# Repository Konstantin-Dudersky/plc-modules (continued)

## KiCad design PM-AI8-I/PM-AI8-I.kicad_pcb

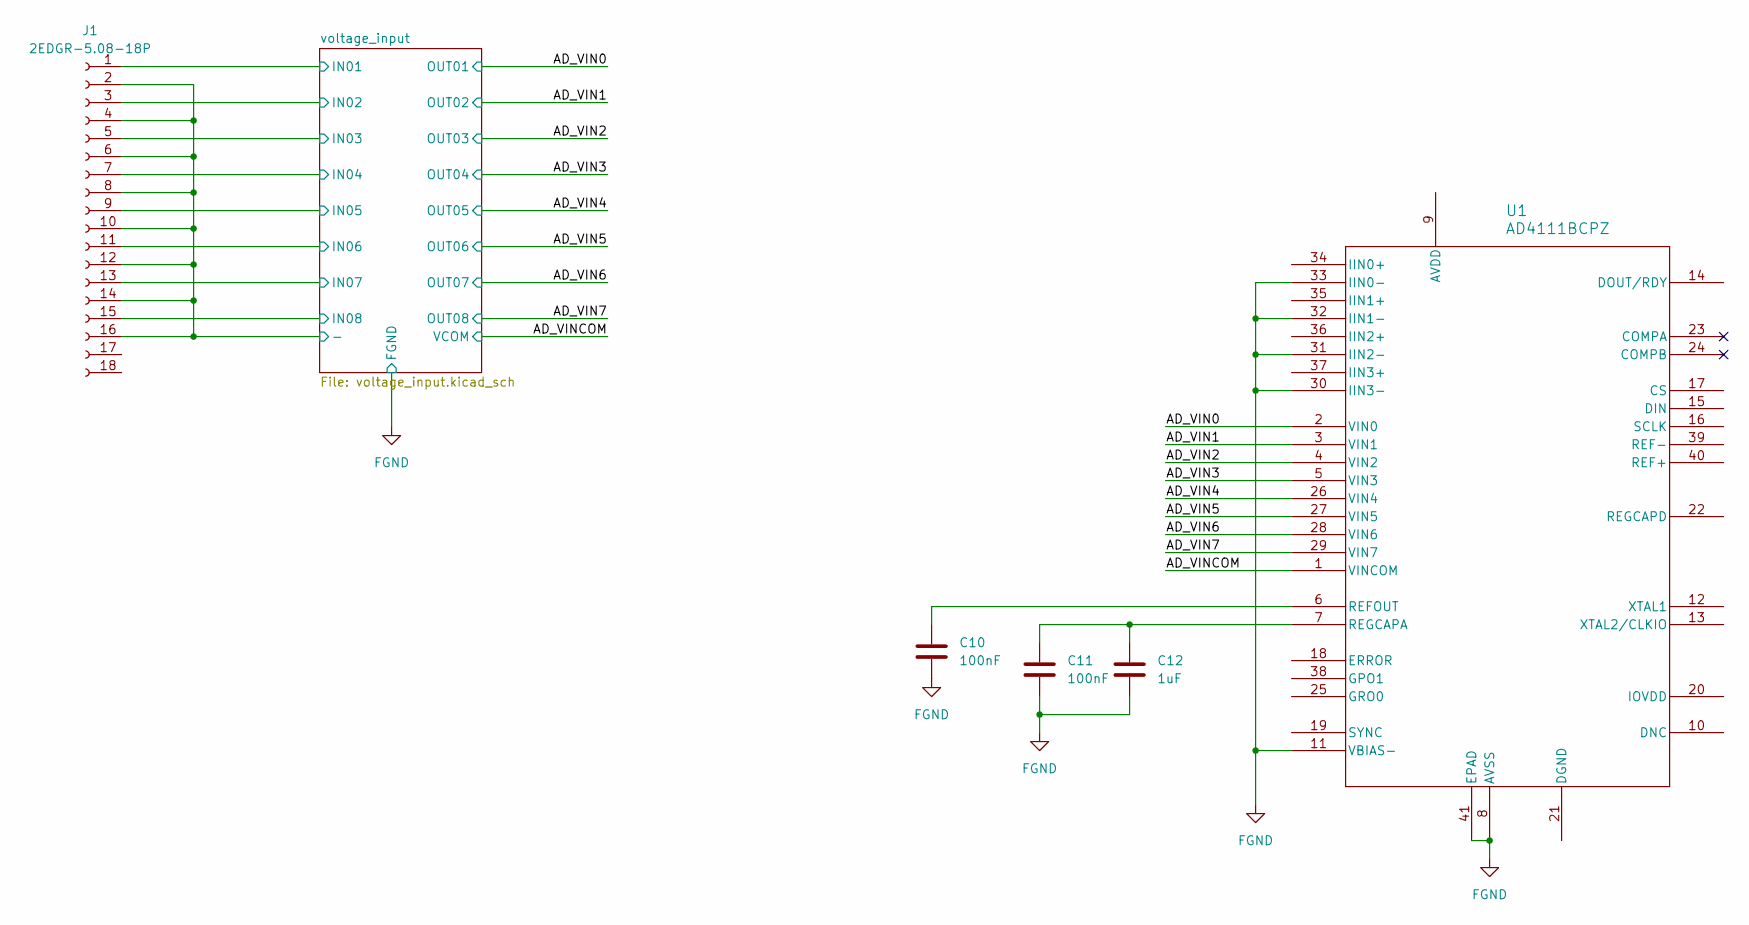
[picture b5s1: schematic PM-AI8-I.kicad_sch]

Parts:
C10, C11: 100nF; C_1206_3216Metric_Pad1.33x1.80mm_HandSolder; part_ipn C_100nF_50V_1206
C12: 1uF; C_1206_3216Metric_Pad1.33x1.80mm_HandSolder; part_ipn C_1uF_50V_1206
J1: 2EDGR-5.08-18P; Degson_2EDGR-5.08-18P; part_ipn 2EDGR-5.08-18P
U1: AD4111BCPZ; AD4111BCPZ_ADI; part_ipn AD4111BCPZ

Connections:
/AD_VIN0: U1.2 (VIN0); also elsewhere on the board
/AD_VIN1: U1.3 (VIN1); also elsewhere on the board
/AD_VIN2: U1.4 (VIN2); also elsewhere on the board
/AD_VIN3: U1.5 (VIN3); also elsewhere on the board
/AD_VIN4: U1.26 (VIN4); also elsewhere on the board
/AD_VIN5: U1.27 (VIN5); also elsewhere on the board
/AD_VIN6: U1.28 (VIN6); also elsewhere on the board
/AD_VIN7: U1.29 (VIN7); also elsewhere on the board
/AD_VINCOM: U1.1 (VINCOM); also elsewhere on the board
/voltage_input/IN01: J1.1; also elsewhere on the board
/voltage_input/IN02: J1.3; also elsewhere on the board
/voltage_input/IN03: J1.5; also elsewhere on the board
/voltage_input/IN04: J1.7; also elsewhere on the board
/voltage_input/IN05: J1.9; also elsewhere on the board
/voltage_input/IN06: J1.11; also elsewhere on the board
/voltage_input/IN07: J1.13; also elsewhere on the board
/voltage_input/IN08: J1.15; also elsewhere on the board
FGND: C10.2, C11.2, C12.2, J1.2, J1.4, J1.6, J1.8, J1.10, J1.12, J1.14, J1.16, U1.8 (AVSS), U1.11 (VBIAS-), U1.30 (IIN3-), U1.31 (IIN2-), U1.32 (IIN1-), U1.33 (IIN0-), U1.41 (EPAD); also elsewhere on the board
unnamed: C10.1, U1.6 (REFOUT)
unnamed: C11.1, C12.1, U1.7 (REGCAPA)

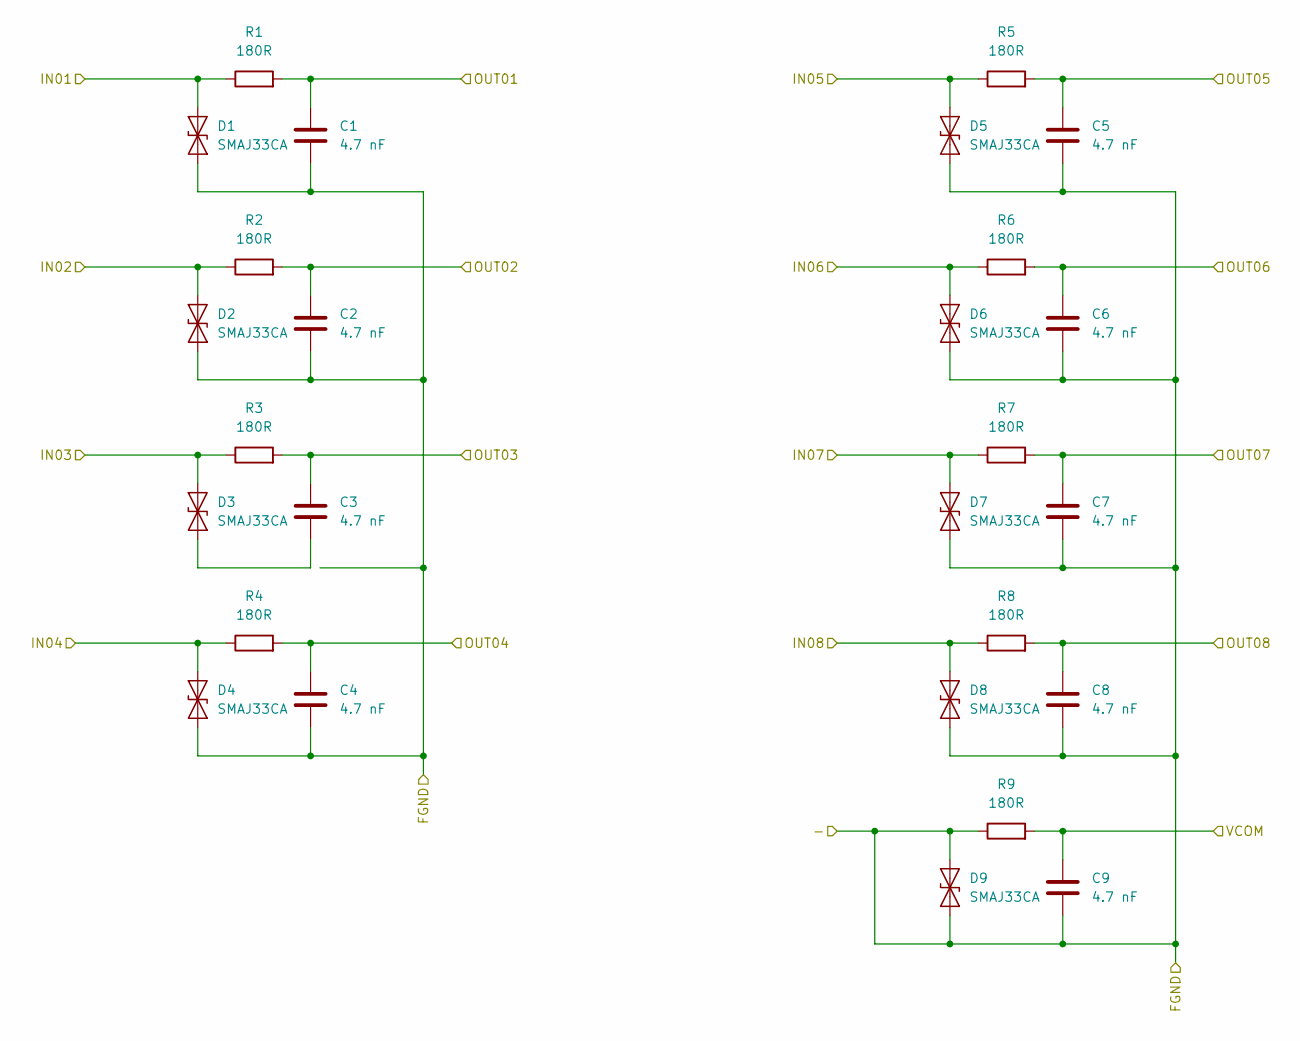
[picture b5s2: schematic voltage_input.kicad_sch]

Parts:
C1, C2, C3, C4, C5, C6, C7, C8, C9: 4.7 nF; C_1206_3216Metric_Pad1.33x1.80mm_HandSolder; part_ipn C_4.7nF_50V_1206
D1, D2, D3, D4, D5, D6, D7, D8, D9: SMAJ33CA; D_SMA
R1, R2, R3, R4, R5, R6, R7, R8, R9: 180R; R_1206_3216Metric_Pad1.30x1.75mm_HandSolder; part_ipn R_180R_1206_1%

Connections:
/AD_VIN0: C1.1, R1.2; also elsewhere on the board
/AD_VIN1: C2.1, R2.2; also elsewhere on the board
/AD_VIN2: C3.1, R3.2; also elsewhere on the board
/AD_VIN3: C4.1, R4.2; also elsewhere on the board
/AD_VIN4: C5.1, R5.2; also elsewhere on the board
/AD_VIN5: C6.1, R6.2; also elsewhere on the board
/AD_VIN6: C7.1, R7.2; also elsewhere on the board
/AD_VIN7: C8.1, R8.2; also elsewhere on the board
/AD_VINCOM: C9.1, R9.2; also elsewhere on the board
/voltage_input/IN01: D1.2 (A2), R1.1; also elsewhere on the board
/voltage_input/IN02: D2.2 (A2), R2.1; also elsewhere on the board
/voltage_input/IN03: D3.2 (A2), R3.1; also elsewhere on the board
/voltage_input/IN04: D4.2 (A2), R4.1; also elsewhere on the board
/voltage_input/IN05: D5.2 (A2), R5.1; also elsewhere on the board
/voltage_input/IN06: D6.2 (A2), R6.1; also elsewhere on the board
/voltage_input/IN07: D7.2 (A2), R7.1; also elsewhere on the board
/voltage_input/IN08: D8.2 (A2), R8.1; also elsewhere on the board
FGND: C1.2, C2.2, C4.2, C5.2, C6.2, C7.2, C8.2, C9.2, D1.1 (A1), D2.1 (A1), D4.1 (A1), D5.1 (A1), D6.1 (A1), D7.1 (A1), D8.1 (A1), D9.1 (A1), D9.2 (A2), R9.1; also elsewhere on the board
unnamed: C3.2, D3.1 (A1)

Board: 2 copper layers, 32 parts (0 on the bottom side), 21 nets, no tracks yet.
